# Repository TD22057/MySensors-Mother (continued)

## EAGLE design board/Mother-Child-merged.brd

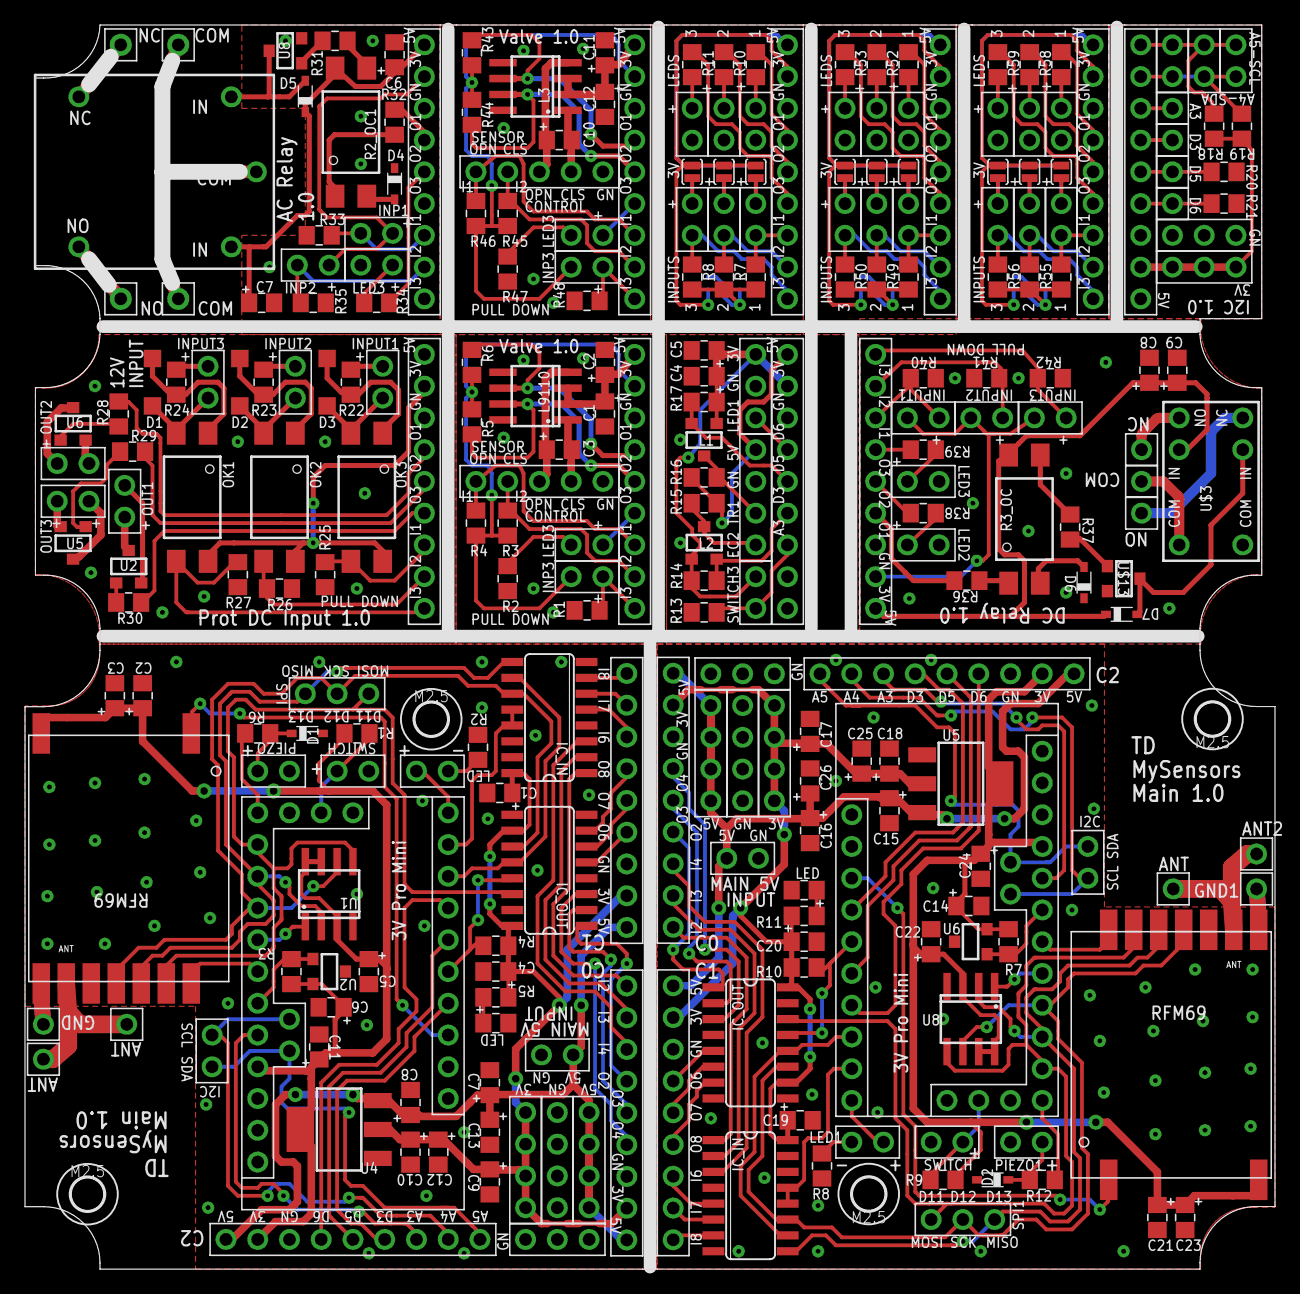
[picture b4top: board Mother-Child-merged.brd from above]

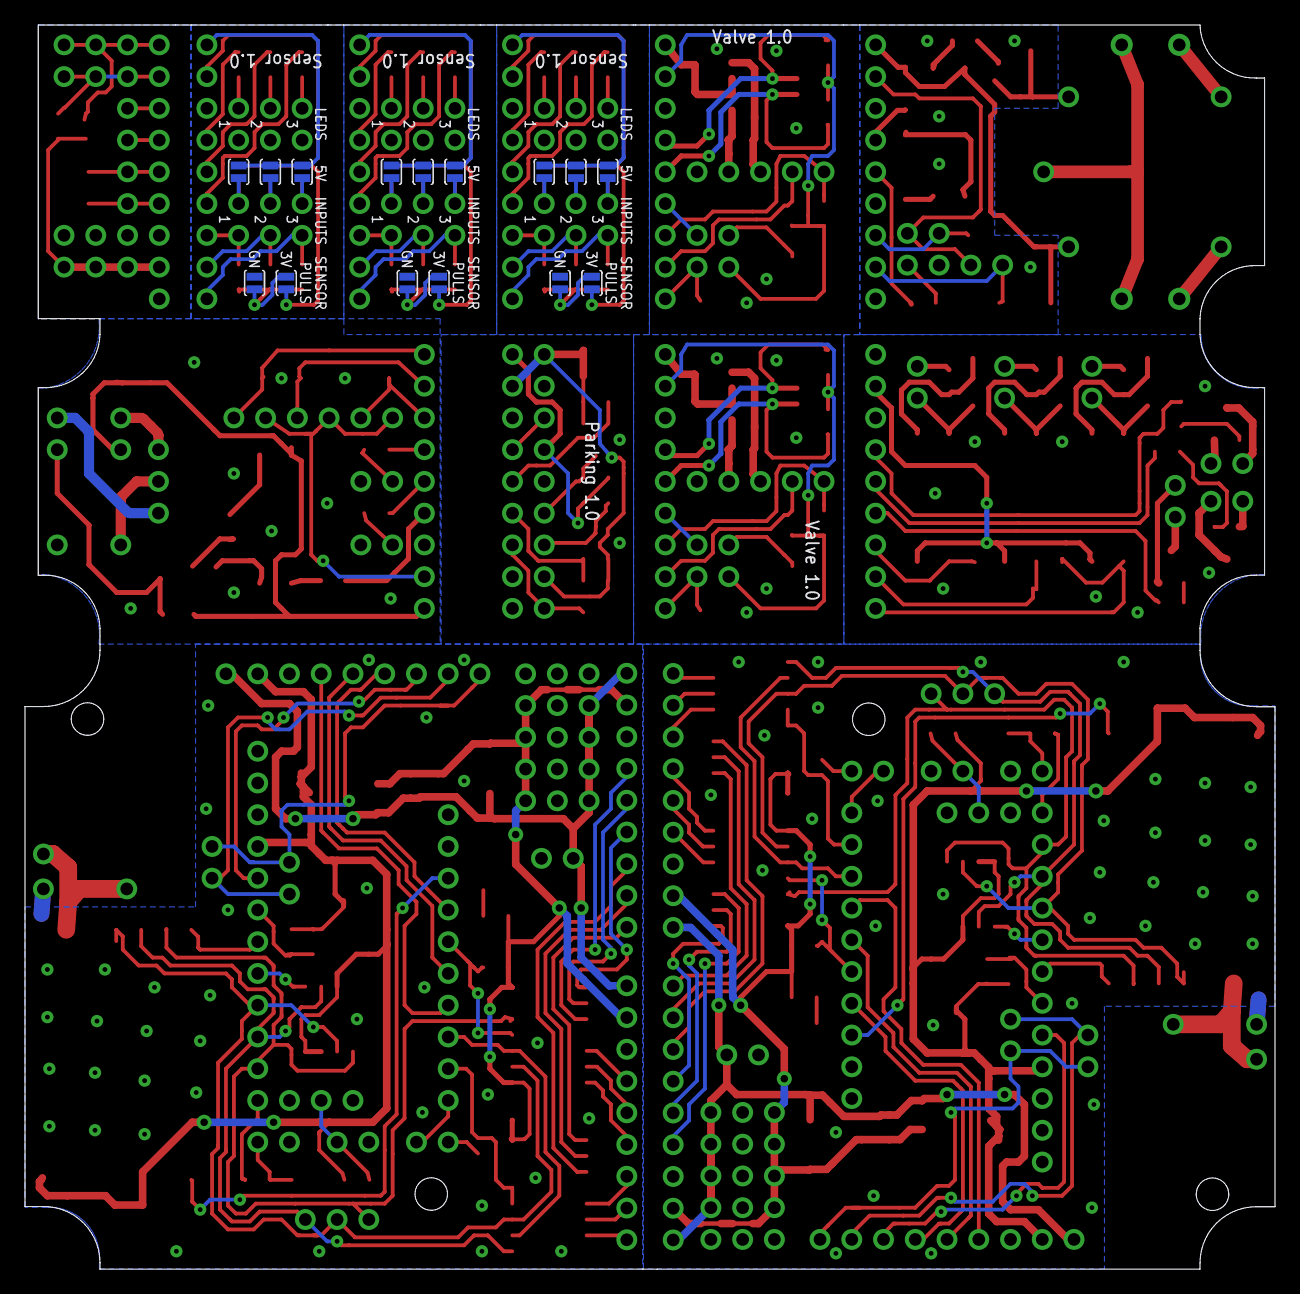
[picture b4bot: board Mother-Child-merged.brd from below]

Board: 4 copper layers, 100.0 x 99.5 mm, 278 parts (15 on the bottom side), 226 nets.

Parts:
ANT, ANT1, ANT2, ANT3: DUPONT_1
C1, C3, C4, C5, C6, C8, C10, C14, C15, C18, C19, C20, C22, C23, C31, C51, C71, C91, C101, C110, C121: 0.1uF; CAP_0805
C2, C7, C9, C11, C12, C13, C16, C17, C21, C24, C25, C26, C27, C41, C61, C81, C111: 10uF; CAP_0805
D1, D2, D4, D5, D6, D7: SOD323
D3, D11, D21: 1N4148; SOD123
GND, GND1: DUPONT_1
H1, H2, H3, H4: HOLE_MOUNTING_M2.5_TIGHT; HOLE_M2.5PAN_TIGHT
I2C, I2C1: DUPONT_2
IC_IN, IC_IN1: SO16
IC_OUT, IC_OUT1: SO16
J3V1, J3V2, J5V, J5V1: DUPONT_4
JGN1, JGN4: DUPONT_4
JGN2, JGN3: DUPONT_3
JINP, JINP1: DUPONT_2
L1, L2: SOT23-3
L3, L9110: L9110 Motor 1; SO-08
LED, LED1: DUPONT_2
LED_SYS, LED_SYS1: LED_0805
OK1, OK2, OK3: SO-4_PC817
PIEZO, PIEZO1: DUPONT_2
PINP1, PINP2, PINP3: DUPONT_2
PRK_DIST: DUPONT_4
PRK_LED: DUPONT_3
PSWITCH: DUPONT_2
R1, R4, R9, R10, R13, R14, R15, R16, R17, R20, R25, R26, R27, R31, R33, R35, R40, R41, R42, R43, R44, R45, R46, R48, R49, R50, R51, R55, R56, R57, R61, R71, R81, R91, R110, R211, R411, R511: 10K; R_0805
R2, R5, R8, R11, R21, R28, R29, R30, R32, R34, R36, R37, R38, R39, R47, R52, R53, R54, R58, R59, R60, R101, R111, R121, R311: 1K; R_0805
R2_LED, R2_SW, R2_SW1, R3_LED, R3_LED1: DUPONT_2
R2_OC1, R3_OC: SO-4_PC817
R2_RELAY: RELAY_SRD_SL_C; RELAY_SRD-SL-C
R3, R7, R22, R23, R24: 4.7K; R_0805
R6, R12: 220; R_0805
R18, R19: 4K7; R_0805
RELAY4, RELAY5, RELAY6: DUPONT_2
RINP4, RINP5, RINP6: DUPONT_2
SENLED1, SENLED2, SENLED3, SENLED4, SENLED5, SENLED6, SENLED7, SENLED8, SENLED9: DUPONT_2
SENSOR1, SENSOR2, SENSOR3, SENSOR4, SENSOR5, SENSOR6, SENSOR7, SENSOR8, SENSOR9, SENSOR10, SENSOR11, SENSOR12, SENSOR13, SENSOR14: DUPONT_2
SJ1, SJ2, SJ3, SJ4, SJ5, SJ6, SJ7, SJ8, SJ9, SJ10, SJ11, SJ12, SJ13, SJ14, SJ15, SJ16, SJ17, SJ18, SJ19, SJ20, SJ21, SJ22, SJ23, SJ24: PAD-JUMPER-2-NO_YES_SILK
SPI, SPI1: DUPONT_3
SWITCH, SWITCH1: DUPONT_2
U1, U8: SO-08
U2, U6, U21, U51, U61: SOT23-3
U3, U7: PRO_MINI_CLONE
U4, U5: AMS1117; SOT223
U$1, U$3, U$6, U$7: DUPONT_MALE90_9
U$2, U$5: RADIO_RFM69W_MS; RFM69W_MS
U$4, U$8, U$41: DUPONT_9
U$9, U$10, U$12, U$111: DUPONT_1_LRG
U$11, U$14, U$18, U$21, U$25, U$26, U$51, U$61, U$71: DUPONT_FEM90_9
U$13, U$81: SOT23-3
U$15, U$16, U$17, U$19, U$20, U$22, U$211: DUPONT_1
U$23, U$24: DUPONT_3
U$31: RELAY_G5V1; RELAY-G5V
VALVE, VALVE1: DUPONT_5
VLV_LED, VLV_LED1: DUPONT_2

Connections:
+3V1: C14.1, C17.1, C18.1, C19.1, C20.1, C21.1, C22.1, C23.1, C24.1, C25.1, IC_IN1.16, IC_OUT1.10, IC_OUT1.16, J3V2.1, J3V2.2, J3V2.3, J3V2.4, R7.2, R9.1, R10.1, R11.1, U5.2, U5.4, U6.2, U7.P$19, U8.3, U8.7, U8.8, U$5.8, U$6.2, U$7.2, U$8.2
+3V3: C1.1, C2.1, C3.1, C4.1, C5.1, C6.1, C9.1, C10.1, C11.1, C12.1, IC_IN.16, IC_OUT.10, IC_OUT.16, J3V1.1, J3V1.2, J3V1.3, J3V1.4, R1.1, R3.2, R4.1, R5.1, U1.3, U1.7, U1.8, U2.2, U3.P$19, U4.2, U4.4, U$1.2, U$2.8, U$3.2, U$4.2
+5V: C7.1, C8.1, C13.1, J5V.1, J5V.2, J5V.3, J5V.4, JINP.1, U4.3, U$1.1, U$3.1, U$4.1
+5V1: C15.1, C16.1, C26.1, J5V1.1, J5V1.2, J5V1.3, J5V1.4, JINP1.1, U5.3, U$6.1, U$7.1, U$8.1
ANALOG1: U7.P$18, U$8.7
ANALOG3: U3.P$18, U$4.7
CRYPT: R3.1, U2.1, U3.P$17
CRYPT1: R7.1, U6.1, U7.P$17
GND: C1.2, C2.2, C3.2, C4.2, C5.2, C6.2, C7.2, C8.2, C9.2, C10.2, C11.2, C12.2, C13.2, D1.A, GND.1, IC_IN.4, IC_IN.8, IC_IN.14, IC_IN.15, IC_OUT.8, JGN1.1, JGN1.2, JGN1.3, JGN1.4, JGN2.1, JGN2.2, JGN2.3, JINP.2, LED_SYS.2, PIEZO.2, R2.1, SWITCH.2, U1.4, U2.3, U3.P$2, U3.P$21, U3.P$27, U4.1, U$1.3, U$2.9, U$2.11, U$3.3, U$4.3
GND1: C14.2, C15.2, C16.2, C17.2, C18.2, C19.2, C20.2, C21.2, C22.2, C23.2, C24.2, C25.2, C26.2, D2.A, GND1.1, IC_IN1.4, IC_IN1.8, IC_IN1.14, IC_IN1.15, IC_OUT1.8, JGN3.1, JGN3.2, JGN3.3, JGN4.1, JGN4.2, JGN4.3, JGN4.4, JINP1.2, LED_SYS1.2, PIEZO1.2, R8.1, SWITCH1.2, U5.1, U6.3, U7.P$2, U7.P$21, U7.P$27, U8.4, U$5.9, U$5.11, U$6.3, U$7.3, U$8.3
I2C_+3V3: R18.1, R19.1, U$18.8, U$24.1, U$24.2, U$24.3
I2C_A3: U$18.3, U$19.1
I2C_D3: U$18.4, U$22.1
I2C_D5: R20.1, U$18.5, U$211.1
I2C_D6: R211.1, U$18.6, U$20.1
I2C_GND: R20.2, R211.2, U$18.7, U$23.1, U$23.2, U$23.3
I2C_SCL: R18.2, SENSOR4.2, SENSOR7.2, SENSOR8.2, U$18.1
I2C_SDA: R19.2, SENSOR4.1, SENSOR7.1, SENSOR8.1, U$18.2
INP1: IC_IN1.5, U$6.7
INP2: IC_IN.1, U$3.9
INP3: IC_IN.2, U$3.8
INP4: IC_IN.3, U$3.7
INP5: IC_IN1.7, U$6.9
INP6: IC_IN.5, U$1.7
INP7: IC_IN.6, U$1.8
INP8: IC_IN.7, U$1.9
INP9: IC_IN1.3, U$7.7
INP10: IC_IN1.1, U$7.9
INP11: IC_IN1.6, U$6.8
INP12: IC_IN1.2, U$7.8
IRQ: U3.P$4, U$4.6
IRQ1: U7.P$4, U$8.6
LED: LED.1, U3.P$10
LED1: LED1.1, U7.P$10
MEMORY_CS: U1.1, U3.P$15
MEMORY_CS1: U7.P$15, U8.1
MISO: IC_IN.9, SPI.3, U1.2, U3.P$13, U$2.13
MISO1: IC_IN1.9, SPI1.3, U7.P$13, U8.2, U$5.13
MOSI: IC_OUT.14, SPI.1, U1.5, U3.P$12, U$2.14
MOSI1: IC_OUT1.14, SPI1.1, U7.P$12, U8.5, U$5.14
unnamed: LED.2, R2.2
unnamed: LED_SYS.1, R5.2
unnamed: D1.C, PIEZO.1, R6.2
unnamed: ANT2.1, ANT3.1, U$5.10
unnamed: LED1.2, R8.2
unnamed: LED_SYS1.1, R11.2
unnamed: D2.C, PIEZO1.1, R12.2
unnamed: PINP1.2, R24.2
unnamed: D21.C, OK2.1, R23.1
unnamed: D21.A, OK2.2, PINP2.1
unnamed: ANT.1, ANT1.1, U$2.10
unnamed: C101.1, L3.4, VALVE1.3
unnamed: D3.C, OK3.1, R22.1
unnamed: D3.A, OK3.2, PINP3.1
unnamed: PINP3.2, R22.2
unnamed: R101.2, SENLED1.1
unnamed: R111.2, SENLED2.1
unnamed: R121.2, SENLED3.1
unnamed: R30.2, U21.1
unnamed: R52.2, SENLED4.1
unnamed: RELAY4.1, U21.3
unnamed: RELAY4.2, U21.2
unnamed: C101.2, L3.1, VALVE1.2
unnamed: R54.2, SENLED6.1
unnamed: SENSOR11.2, SJ13.1, SJ14.1
unnamed: SENSOR3.2, SJ5.1, SJ6.1
unnamed: SENSOR2.2, SJ3.1, SJ4.1
unnamed: R29.2, U51.1
unnamed: R28.2, U61.1
unnamed: R3_LED1.1, R39.1
unnamed: C31.1, L9110.4, VALVE.3
unnamed: RELAY5.2, U51.2
unnamed: RELAY6.1, U61.3
unnamed: RELAY6.2, U61.2
unnamed: R2_LED.1, R34.1
unnamed: D5.A, R2_RELAY.2, U$81.3
unnamed: R311.2, U$81.1
unnamed: R2_OC1.3, R311.1
unnamed: D4.A, R2_OC1.2
unnamed: R2_OC1.1, R32.1
unnamed: C31.2, L9110.1, VALVE.2
unnamed: R37.2, U$13.1
unnamed: R3_OC.3, R37.1
unnamed: D6.A, R3_OC.2
unnamed: R3_OC.1, R36.1
unnamed: R3_LED.1, R38.1
unnamed: U$16.1, U$31.5
unnamed: SENSOR1.2, SJ1.1, SJ2.1
unnamed: SENSOR10.2, SJ11.1, SJ12.1
unnamed: SENSOR9.2, SJ9.1, SJ10.1
unnamed: R21.1, VLV_LED.2
unnamed: R59.2, SENLED8.1
unnamed: R60.2, SENLED9.1
unnamed: SENSOR14.2, SJ21.1, SJ22.1
unnamed: SENSOR13.2, SJ19.1, SJ20.1
unnamed: SENSOR12.2, SJ17.1, SJ18.1
unnamed: D11.C, OK1.1, R24.1
unnamed: D11.A, OK1.2, PINP1.1
unnamed: PINP2.2, R23.2
unnamed: R47.1, VLV_LED1.2
unnamed: R53.2, SENLED5.1
unnamed: RELAY5.1, U51.3
unnamed: D7.A, U$13.3, U$31.9
unnamed: R58.2, SENLED7.1
OUT1: IC_OUT1.1, U$7.6
OUT2: IC_OUT.1, U$3.6
OUT3: IC_OUT.2, U$3.5
OUT4: IC_OUT.3, U$3.4
OUT5: IC_OUT1.2, U$7.5
OUT6: IC_OUT.5, U$1.4
OUT7: IC_OUT.6, U$1.5
OUT8: IC_OUT.7, U$1.6
OUT9: IC_OUT1.3, U$7.4
OUT10: IC_OUT1.5, U$6.4
OUT11: IC_OUT1.7, U$6.6
OUT12: IC_OUT1.6, U$6.5
PARK_+3V3: C41.1, C51.1, L1.1, L2.1, PRK_LED.1, PSWITCH.2, R14.2, R17.2, U$41.8
PARK_+5V: PRK_DIST.1, R15.2, R16.2, U$41.9
PARK_ECHO: L2.2, R14.1, U$41.4
PARK_ECHO_5V: L2.3, PRK_DIST.4, R15.1
PARK_GND: C41.2, C51.2, PRK_DIST.2, PRK_LED.2, R13.2, U$41.7
PARK_RING: PRK_LED.3, U$41.6
PARK_SWITCH: PSWITCH.1, R13.1, U$41.3
PARK_TRIGGER: L1.2, R17.1, U$41.5
PARK_TRIGGER_5V: L1.3, PRK_DIST.3, R16.1
PIEZO: R6.1, U3.P$11
PIEZO1: R12.1, U7.P$11
PROT_+3V3: OK1.4, OK2.4, OK3.4, U$11.8
PROT_GND: R25.1, R26.1, R27.1, U$11.7
PROT_INPUT1: OK1.3, R27.2, U$11.1
PROT_INPUT2: OK2.3, R26.2, U$11.2
PROT_INPUT3: OK3.3, R25.2, U$11.3
PROT_RELAY1: R30.1, U$11.4
PROT_RELAY2: R29.1, U$11.5
PROT_RELAY3: R28.1, U$11.6
PWM1: U3.P$6, U$4.5
PWM2: U3.P$7, U$4.4
PWM3: U7.P$7, U$8.4
PWM4: U7.P$6, U$8.5
R2_COM: R2_RELAY.3, U$10.1, U$12.1
R2_NC: R2_RELAY.5, U$111.1
R2_NC1: U$17.1, U$31.1
R2_NO: R2_RELAY.4, U$9.1
R2_NO1: U$15.1, U$31.10
RADIO_CS: U3.P$16, U$2.15
RADIO_CS1: U7.P$16, U$5.15
RADIO_IRQ: U3.P$3, U$2.2
RADIO_IRQ1: U7.P$3, U$5.2
REL_AC_+3V3: R2_SW.2, R2_SW1.2, U$71.8
REL_AC_+5V: C61.1, C71.1, D5.C, R2_OC1.4, R2_RELAY.1, U$71.9
REL_AC_GND: C61.2, C71.2, D4.C, R2_LED.2, R33.2, R35.2, U$71.7, U$81.2
REL_AC_INP1: R2_SW1.1, R33.1, U$71.3
REL_AC_INP2: R2_SW.1, R35.1, U$71.2
REL_AC_LED2: R34.2, U$71.5
REL_AC_RELAY: R32.2, U$71.6
REL_DC_+3V3: RINP4.2, RINP5.2, RINP6.2, U$14.8
REL_DC_+5V: C81.1, C91.1, D7.C, R3_OC.4, U$14.9, U$31.2
REL_DC_CTRL1: R36.2, U$14.6
REL_DC_GND: C81.2, C91.2, D6.C, R3_LED.2, R3_LED1.2, R40.2, R42.2, R411.2, U$13.2, U$14.7
REL_DC_INP1: R40.1, RINP4.1, U$14.3
REL_DC_INP2: R411.1, RINP5.1, U$14.2
REL_DC_INP3: R42.1, RINP6.1, U$14.1
REL_DC_LED2: R38.2, U$14.5
REL_DC_LED3: R39.2, U$14.4
SCK: IC_IN.11, IC_OUT.11, SPI.2, U1.6, U3.P$14, U$2.12
SCK1: IC_IN1.11, IC_OUT1.11, SPI1.2, U7.P$14, U8.6, U$5.12
SCL: I2C.2, U3.P$24, U$4.9
SCL1: I2C1.2, U7.P$24, U$8.9
SDA: I2C.1, U3.P$23, U$4.8
SDA1: I2C1.1, U7.P$23, U$8.8
SENSOR_1: R71.1, SENSOR1.1, U$61.3
SENSOR_2: R81.1, SENSOR2.1, U$61.2
SENSOR_3: R91.1, SENSOR3.1, U$61.1
SENSOR_4: R49.1, SENSOR9.1, U$25.3
SENSOR_5: R50.1, SENSOR10.1, U$25.2
SENSOR_6: R511.1, SENSOR11.1, U$25.1
SENSOR_7: R55.1, SENSOR12.1, U$26.3
SENSOR_8: R56.1, SENSOR13.1, U$26.2
SENSOR_9: R57.1, SENSOR14.1, U$26.1
SENSOR_+3V1: SJ9.2, SJ11.2, SJ13.2, SJ15.2, U$25.8
SENSOR_+3V2: SJ17.2, SJ19.2, SJ21.2, SJ23.2, U$26.8
SENSOR_+3V3: SJ1.2, SJ3.2, SJ5.2, SJ7.2, U$61.8
SENSOR_+5V: SJ2.2, SJ4.2, SJ6.2, U$61.9
SENSOR_+5V1: SJ10.2, SJ12.2, SJ14.2, U$25.9
SENSOR_+5V2: SJ18.2, SJ20.2, SJ22.2, U$26.9
SENSOR_GND: SENLED1.2, SENLED2.2, SENLED3.2, SJ8.2, U$61.7
SENSOR_GND1: SENLED4.2, SENLED5.2, SENLED6.2, SJ16.2, U$25.7
SENSOR_GND2: SENLED7.2, SENLED8.2, SENLED9.2, SJ24.2, U$26.7
SENSOR_LED1: R101.1, U$61.6
SENSOR_LED2: R111.1, U$61.5
SENSOR_LED3: R121.1, U$61.4
SENSOR_LED4: R53.1, U$25.5
SENSOR_LED5: R52.1, U$25.6
SENSOR_LED6: R54.1, U$25.4
SENSOR_LED7: R59.1, U$26.5
SENSOR_LED8: R58.1, U$26.6
SENSOR_LED9: R60.1, U$26.4
SENSOR_PULL: R71.2, R81.2, R91.2, SJ7.1, SJ8.1
SENSOR_PULL1: R49.2, R50.2, R511.2, SJ15.1, SJ16.1
SENSOR_PULL2: R55.2, R56.2, R57.2, SJ23.1, SJ24.1
SHIFT_CS: IC_IN.10, IC_OUT.12, U3.P$8
SHIFT_CS1: IC_IN1.10, IC_OUT1.12, U7.P$8
SHIFT_IN_LOAD: IC_IN.12, IC_IN.13, U3.P$9
SHIFT_IN_LOAD1: IC_IN1.12, IC_IN1.13, U7.P$9
SHIFT_OUT_ENABLE: IC_OUT.13, R4.2, U3.P$5
SHIFT_OUT_ENABLE1: IC_OUT1.13, R10.2, U7.P$5
SWITCH: R1.2, SWITCH.1, U3.P$26
SWITCH1: R9.2, SWITCH1.1, U7.P$26
VALVE_+3V1: R43.1, R44.1, R45.1, R46.1, SENSOR6.2, U$51.8
VALVE_+3V3: R31.1, R41.1, R51.1, R61.1, SENSOR5.2, U$21.8
VALVE_+5V: C27.1, C110.1, L9110.2, L9110.3, U$21.9
VALVE_+5V1: C111.1, C121.1, L3.2, L3.3, U$51.9
VALVE_CLOSED: R31.2, U$21.2, VALVE.4
VALVE_CLOSED1: R45.2, U$51.2, VALVE1.4
VALVE_CONTROL1: L9110.6, R61.2, U$21.6
VALVE_CONTROL2: L9110.7, R51.2, U$21.5
VALVE_CONTROL3: L3.6, R43.2, U$51.6
VALVE_CONTROL4: L3.7, R44.2, U$51.5
VALVE_GND: C27.2, C110.2, L9110.5, L9110.8, R21.2, R110.2, U$21.7, VALVE.1
VALVE_GND1: C111.2, C121.2, L3.5, L3.8, R47.2, R48.2, U$51.7, VALVE1.1
VALVE_LED: U$21.4, VLV_LED.1
VALVE_LED1: U$51.4, VLV_LED1.1
VALVE_OPENED: R41.2, U$21.3, VALVE.5
VALVE_OPENED1: R46.2, U$51.3, VALVE1.5
VALVE_SENSOR1: R48.1, SENSOR6.1, U$51.1
VALVE_SENSOR3: R110.1, SENSOR5.1, U$21.1

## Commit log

2016-02-06 Fixed typos
2016-02-06 Added license comment
2016-02-07 Fixed permissions
2016-02-09 Added pdf versions
